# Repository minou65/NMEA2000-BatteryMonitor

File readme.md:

# NMEA Battery monitor

## Table of contents
- [NMEA Battery monitor](#nmea-battery-monitor)
	- [Table of contents](#table-of-contents)
	- [Description](#description)
	- [Disclaimer](#disclaimer)
	- [Schema](#schema)
	- [NMEA 2000](#nmea-2000)
	- [Librarys](#librarys)
	- [Part list](#part-list)
		- [Shunt housing](#shunt-housing)
	- [Running values](#running-values)
		- [Battery voltage](#battery-voltage)
		- [Current](#current)
		- [Avg current](#avg-current)
		- [State of charge (Soc)](#state-of-charge-soc)
		- [Time to go (Ttg)](#time-to-go-ttg)
		- [Battery full](#battery-full)
		- [Temperature](#temperature)
	- [Statistics](#statistics)
	- [Configuration](#configuration)
		- [System configuration](#system-configuration)
			- [Thing name](#thing-name)
			- [AP password](#ap-password)
			- [WiFi SSID](#wifi-ssid)
			- [WiFi password](#wifi-password)
			- [start AP only at boot sequence](#start-ap-only-at-boot-sequence)
			- [AP offline mode after (minutes)](#ap-offline-mode-after-minutes)
		- [NEMA configuration](#nema-configuration)
			- [Instance](#instance)
			- [SID](#sid)
		- [Shunt settings](#shunt-settings)
			- [Shunt resistance \[Ω\] __\*__](#shunt-resistance-ω-)
			- [Expected max current \[A\] __\*__](#expected-max-current-a-)
			- [Voltage calibration factor](#voltage-calibration-factor)
			- [Current calibration factor](#current-calibration-factor)
		- [Battery](#battery)
			- [Type __\*__](#type-)
			- [Voltage __\*__](#voltage-)
			- [Chemistry __\*__](#chemistry-)
			- [Capacity __\*__](#capacity-)
			- [charge efficiency \[%\]](#charge-efficiency-)
			- [Minimum SOC \[%\]](#minimum-soc-)
			- [Replacement date](#replacement-date)
			- [Manufacturer](#manufacturer)
		- [Battery full detection](#battery-full-detection)
			- [Voltage when full \[V\] __\*__](#voltage-when-full-v-)
			- [Tail current \[A\] __\*__](#tail-current-a-)
			- [Delay before full \[s\] __\*__](#delay-before-full-s-)
			- [Current threshold](#current-threshold)
			- [Statistics Page](#statistics-page)
	- [Username and password](#username-and-password)
	- [Default IP address](#default-ip-address)
	- [Firmware Update](#firmware-update)
	- [Blinking codes](#blinking-codes)
	- [Reset](#reset)

## Description
The INA226 is a versatile current and power monitor chip that can be used to create a battery monitor. It measures both voltage and current, taking into account the direction of current flow (whether it’s from or to the battery). Based on the configured ampere-hours (Ah), current, and voltage, it calculates the battery's state of charge.

Here are some key details about the INA226:
- Voltage Measurement Range: 0V to 36V DC
- Shunt Voltage Range (for current measurement): ±82mV
- The INA226 can handle shunt voltages as low as 60mV and as high as 82mV, depending on the current and the shunt resistor used

The INA226 should be connected to the shunt so that charges going into the battery are positive and those coming out of the battery are negative.

 The system communicates via the NMEA 2000 protocol, sending temperature values and alarms as NMEA 2000 messages over an NMEA bus. Configuration is done through a web interface, and real-time values can be viewed on a website. Additionally, there's a link on the configuration page for convenient firmware updates.

 ## Disclaimer
 | | |
 |-|-----------------|
 |  | Always use a fuse in the + line from the battery to the sensor!! |
 |  | Be careful when using metal tools in the vicinity of batteries. Dropping a metal tool onto a battery might cause a short circuit and possibly an explosion. |

## Schema

## NMEA 2000
The following PGN's will be send
- 127506
- 127508
- 127513

## Librarys 

The Software has been created using Visual Studio with the addon Visual Micro. In order to build it you also need some libraries.

- Wire
- [OneWire (2.3.7)](https://github.com/PaulStoffregen/OneWire)
- [DallasTemperature (3.9.0)](https://github.com/milesburton/Arduino-Temperature-Control-Library)
- [NMEA2000](https://github.com/ttlappalainen/NMEA2000)
- [NMEA2000_ESP32](https://github.com/ttlappalainen/NMEA2000_esp32)
- [AsyncTCP (3.2.6) __*__](https://github.com/mathieucarbou/AsyncTCP)
- [ESPAsyncWebServer (3.3.12) __*__](https://github.com/mathieucarbou/ESPAsyncWebServer)
- [WebSerial (2.0.7) __*__](https://github.com/ayushsharma82/WebSerial)
- [IotWebConf](https://github.com/minou65/IotWebConf)
- [IotWebConfAsync (1.0.2) __*__](https://github.com/minou65/IotWebConfAsync)
- [IotWebRoot](https://github.com/minou65/IotWebRoot)
- [ArduinoJson](https://github.com/bblanchon/ArduinoJson)
- [Preferences](https://github.com/espressif/arduino-esp32/tree/master/libraries/Preferences) (ESP32 built-in)
- [WiFi](https://github.com/espressif/arduino-esp32/tree/master/libraries/WiFi) (ESP32 built-in)
- [Update](https://github.com/espressif/arduino-esp32/tree/master/libraries/Update) (ESP32 built-in)

__*__ new version and/or new repo

## Part list
| Part | Value | Supplier |
| --- | --- | --- |
| D1 | 1N4001 | Reichelt |
| ESP1 | ESP32DEVKITV1 | [ebay](https://www.ebay.ch/itm/204191675506?var=504772734176) |
| IC1 | R-78E05-1.0 | Reichelt |
| IC2 | INA226 | [ebay](https://www.ebay.ch/itm/314750066199) |
| IC3 | MCP2562 | Reichelt oder [ebay](https://www.ebay.ch/itm/364610349378) |
| R1 | 4.7k | Reichelt |
| R2 | Shunt | [ebay](https://www.ebay.ch/itm/164378822180?var=463997139291) |
| X1 | AKL 057-03 | Reichelt |
| X2 | AKL 057-02 | Reichelt |
| X3 | PSS 254/3G | Reichelt |

__Before you can use the sensor board you have to remove the shunt resistor soldered to that board and instead use a bigger shunt, e.g. a 100A/75mV.__

You also need a __shunt__, since the small resistor on the board (__dont forget to remove it!__) will not survive the high currents.
There are plenty of options out there. Make sure that you select a resistor appropriate for the currents you expect. I'm using a 100A/75mV shunt.

If you have a 48V System, be aware of the fact that the INA226 does only support voltages up to 36V (40V max). You need a voltage divider to make shure your sensor is not destroyed. 
The code assumes that you use a __470KOhm and a 1MOhm__ resistor, measuring across the 1MOhm towards GND. `( + --470K-- --1M -- GND )` The smaller you choose the small resistor in comparison to the bigger one, the more accurate the measurement will be.

### Shunt housing
In the stl folder you will find a housing for the shunt.

## Running values
### Battery voltage

### Current
Current in amperes flowing through the shunt. If the current is positiv, the battery is being charged. If it is negative, the battery is being discharged.
See [Current calibration factor](#current-calibration-factor) for more information.

### Avg current
The average current consumption in the last 60 seconds.

### State of charge (Soc)
Shows the charge level of the battery. This is calculated based on the capacity and the Ah consumed and is an estimate based on the current consumption.

If no shunt is used and the current calibration factor is set to 0, the following table is used to calculate the Soc

### Time to go (Ttg)
If the time is 00:00, then the battery is charging. Otherwise, it will display an estimate in hours and minutes of how long, based on the current consumption, it will take until the battery is empty.

### Battery full
true or false

### Temperature

## Statistics

## Configuration
After the first boot, there are some values needs to be set up.
These items are maked with __*__ (star) in the list below.

### System configuration

#### Thing name
Please change the name of the device to a name you think describes it the most. It is advised to incorporate a location here in case you are planning to set up multiple devices in the same area. You should only use english letters, and the "_" underscore character. Thus, must not use Space, dots, etc. E.g. `main_cabin` __*__

#### AP password
This password is used, when you want to access the device later on. You must provide a password with at least 8, at most 32 characters. You are free to use any characters, further more you are encouraged to pick a password at least 12 characters long containing at least 3 character classes. __*__

#### WiFi SSID
The name of the WiFi network you want the device to connect to. __*__

#### WiFi password
The password of the network above. Note, that unsecured passwords are not supported in your protection. __*__

#### start AP only at boot sequence
This checkbox, when selected, ensures that the Access Point (AP) is initiated only after the system's boot sequence for the time set in the Startup delay. This can be useful for optimizing system performance and security by preventing the AP from starting at other times, which could potentially lead to unauthorized access or unnecessary resource consumption.

The difference to the setting AP offline mode is that after a successful connection to a WiFi, if the connection is lost, it will not fall back to AP mode.

#### AP offline mode after (minutes)
If you don’t plan to connect the sensor to a WiFi network, you don’t need to configure the two options above. If you want to disable the WiFi after a certain time, you can use this option. Specify how long the WiFi should remain enabled after turning on the sensor. Valid values are from 0 to 30 minutes. A value of 0 means that WiFi is always enabled.

### NEMA configuration
#### Instance
This should be unique at least on one device. May be best to have it unique over all devices sending this PGN. A total of 5 instances are occupied by the device, starting with the number set here. __*__

#### SID
Sequence identifier. In most cases you can use just 255 for SID. The sequence identifier field is used to tie different PGNs data together to same sampling or calculation time.

### Shunt settings
#### Shunt resistance [Ω] __*__
```
R = U / I

U in V
I in A
R in Ohm
```

Assuming a voltage of 75 mV at nominal current, the resulting resistance in ohms will be as follows:

| Shunt Current | Resistance in Ohm | Remarks |
| --- | --- | --- |
| 2 | 100 | Original resistor on the board. |
| 50A | 1.500 |
| 100A | 0.750 |
| 200A | 0.375 |
| 300A | 0.250 |

#### Expected max current [A] __*__
Maximum current that may flow through the shunt

#### Voltage calibration factor
Use a multimeter to measure the voltage on the battery. The measured voltage divided by the voltage displayed by the battery monitor gives the factor that you enter here.

#### Current calibration factor
Use a multimeter to measure the current at the shunt. The measured current, divided by the current displayed by the battery monitor, gives the factor that you need to enter here.

Normally a positive current means that the battery is being charged, a negative current means that it is being discharged. If this is the other way round due to incorrect installation of the shunt, the current can be "reversed" by a negative factor.

If this value is set to 0, no current will be measured. This can be useful if no shunt is installed, such as in a starter battery where only voltage and temperature need to be monitored. See also [State of charge (Soc)](#state-of-charge-soc).

### Battery
#### Type __*__
one of the following
- flooded
- gel
- AGM

#### Voltage __*__
- 6V
- 12V
- 24V
- 32V
- 62V
- 42V
- 48V

Please note that the sensor is built for a maximum voltage of 40V without any special measures!

#### Chemistry __*__
- lead acid
- LiIon
- NiCad
- NiMh

#### Capacity __*__
This parameter is used to tell the battery monitor how big the battery is.

The setting is the battery capacity in Amp-hours (Ah).

#### charge efficiency [%] 
The "Charge Efficiency Factor" compensates for the capacity (Ah) losses during charging. A setting of 100% means that there are no losses.
A charge efficiency of 95% means that 10Ah must be transferred to the battery to get 9.5Ah actually stored in the battery. The charge efficiency of a 
battery depends on battery type, age and usage. The battery monitor takes this phenomenon into account with the charge efficiency factor.

The charge efficiency of a lead acid battery is almost 100% as long as no gas generation takes place. Gassing means that part of the charge current 
is not transformed into chemical energy, which is stored in the plates of the battery, but is used to decompose water into oxygen and hydrogen 
gas (highly explosive!). The energy stored in the plates can be retrieved during the next discharge, whereas the energy used to decompose water is lost. 
Gassing can easily be observed in flooded batteries. Please note that the ‘oxygen only’ end of the charge phase of sealed (VRLA) gel 
and AGM batteries also results in a reduced charge efficiency.

#### Minimum SOC [%]
The minimum SoC is the lowest level of charge that a battery can safely operate at without damaging its cells or reducing its capacity. It is usually expressed as a percentage of the maximum charge. For example, if a battery has a minimum SoC of 10%, it means that it should not be discharged below 10% of its full capacity.

#### Replacement date
The replacement date is the date when the battery was replaced with a new one. It is only for documentation

#### Manufacturer
Manufacturer can be used for documentation

### Battery full detection
#### Voltage when full [V] __*__
The battery voltage must be above this voltage level to consider the battery as fully charged. As soon as the battery monitor detects that the 
voltage of the battery has reached this "charged voltage" parameter and the current has dropped below the "tail current" parameter for a certain 
amount of time, the battery monitor will set the state of charge to 100%.

The following table can help set the correct value

| Type | fully charged |
| --- | --- |
| 12V lead acid | 12.85V |
| 12V AGM | 12.85V |
| 12V LiIon | 12.65V |

#### Tail current [A] __*__
The battery is considered as fully charged once the charge current has dropped to less than this "Tail current" parameter. 
The "Tail current" parameter is expressed as a percentage of the battery capacity.

Note that some battery chargers stop charging when the current drops below a set threshold. In these cases, the tail current must be set 
higher than this threshold.

As soon as the battery monitor detects that the voltage of the battery has reached the set "Charged voltage" parameter and the current has 
dropped below this "Tail current" parameter for a certain amount of time, the battery monitor will set the state of charge to 100%.

#### Delay before full [s] __*__
This is the time the "Voltage when full [V]" parameter and the "Tail current [A]" parameter must be met in order to consider the battery fully charged.

#### Current threshold
When the current measured falls below the "Current threshold" parameter it will be considered zero. The "Current threshold" is used to cancel out very small currents that can negatively affect the long-term state of charge readout in noisy environments. For example, if the actual long-term current is 0.0A and, due to injected noise or small offsets, the battery monitor measures ­0.05A the battery monitor might, in the long term, incorrectly indicate that the battery is empty or will need to be recharged. When the current threshold in this example is set to 0.1A, the battery monitor calculates with 0.0A so that errors are eliminated.

#### Statistics Page

The Statistics page provides detailed information about the performance and status of your device. Here are the key metrics displayed on this page:

- **Min Volt**: Displays the minimum voltage recorded, e.g., 10.5V.
- **Max Volt**: Displays the maximum voltage recorded, e.g., 13.4V.
- **Charged Energy**: Indicates the total energy charged, measured in kWh.
- **Discharged Energy**: Indicates the total energy discharged, measured in kWh.
- **Total Ah Drawn**: Shows the total ampere-hours drawn.
- **Last Discharged Energy**: Displays the energy discharged during the last cycle.
- **Deepest Discharged Energy**: Shows the deepest discharge recorded.
- **Min Temperature**: Displays the minimum temperature recorded.
- **Max Temperature**: Displays the maximum temperature recorded.
- **Charge Cycles**: Indicates the number of charge cycles completed.
- **Auto Syncs**: Shows the number of automatic synchronizations. Auto Syncs occur every time the sensor detects that the battery is full. In this case, the State of Charge (SOC) is set to 100%.
- **Time Since Last Full**: Displays the time elapsed since the battery was last fully charged.

Additionally, there is a **Reset Statistics** button available on this page. Pressing this button will reset all the recorded statistics to their default values. This can be useful for starting fresh measurements or troubleshooting purposes.

These statistics help you monitor the health and performance of your device, ensuring it operates efficiently and effectively.

## Username and password
Username is admin. when not connected to an AP the default password is 123456789.

## Default IP address
When in AP mode, the default IP address is 192.168.4.1

## Firmware Update
To update the firmware, navigate to the Configuration page and click on the Firmware Update link. Follow the on-screen instructions to complete the update process.

## Blinking codes
Previous chapters mentioned blinking patterns, now here is a table summarizing the meaning of the blink codes.

| Blinking Pattern | Meaning |
| --- | --- |
| Rapid blinking <br>(mostly on, interrupted by short off periods) | Entered Access Point mode. This means the device creates its own WiFi network. You can connect to the device with your smartphone or WiFi capable computer. |
| Alternating on/off blinking | Trying to connect to the configured WiFi network. |
| Mostly off with occasional short flash | The device is online. |
| Mostly off with occasional long flash | The device is in offline mode |

## Reset
When CONFIG_PIN is pulled to ground on startup, the Thing will use the initial
password to buld an AP. (E.g. in case of lost password)

Reset pin is GPIO 13

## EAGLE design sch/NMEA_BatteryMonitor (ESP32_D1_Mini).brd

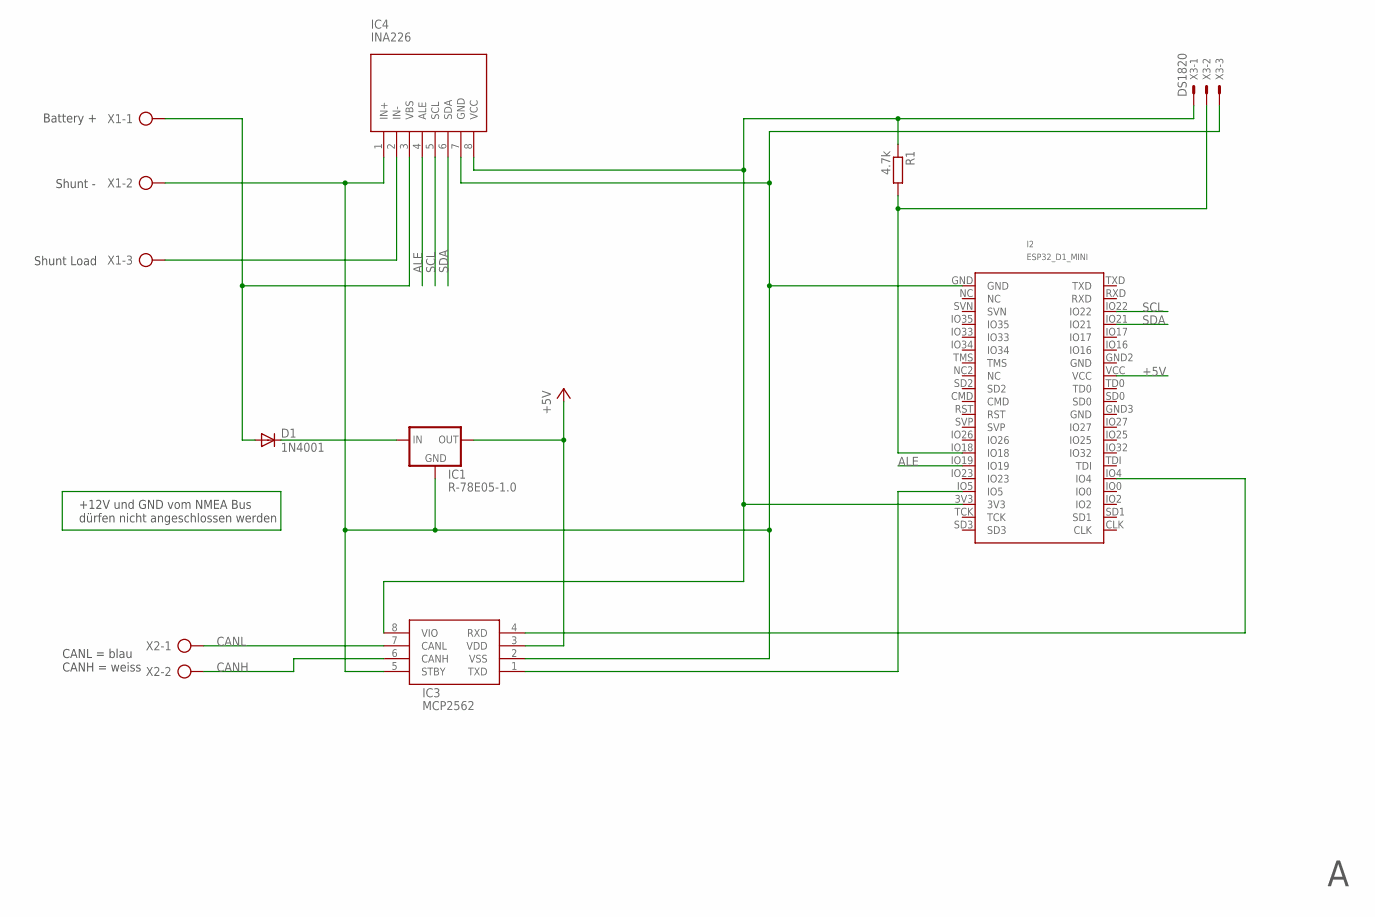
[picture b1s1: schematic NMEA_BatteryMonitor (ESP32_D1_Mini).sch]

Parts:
D1: 1N4001; SOD80
I2: ESP32_D1_MINI
IC1: R-78E05-1.0; R-78E-XX1.0
IC3: MCP2562; SO-8
IC4: INA226
R1: 4.7k; R0805
X1: AK500/3
X2: AK500/2
X3: DS1820; 22-23-2031

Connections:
12V: D1.A, IC4.3 (VBS), X1.1
+5V: I2.VCC, IC1.OUT, IC3.3 (VDD)
ALE: I2.IO19, IC4.4 (ALE)
CANH: IC3.6 (CANH), X2.2
CANL: IC3.7 (CANL), X2.1
GND: I2.GND, IC1.GND, IC3.2 (VSS), IC3.5 (STBY), IC4.1 (IN+), IC4.7 (GND), X1.2, X3.3
LOAD: IC4.2 (IN-), X1.3
unnamed: I2.IO4, IC3.4 (RXD)
unnamed: I2.IO5, IC3.1 (TXD)
unnamed: I2.3V3, IC3.8 (VIO), IC4.8 (VCC), R1.1, X3.1
unnamed: D1.C, IC1.IN
unnamed: I2.IO18, R1.2, X3.2
SCL: I2.IO22, IC4.5 (SCL)
SDA: I2.IO21, IC4.6 (SDA)

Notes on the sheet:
CANL = blau CANH = weiss
Shunt -
Shunt Load
Battery +
+12V und GND vom NMEA Bus dürfen nicht angeschlossen werden

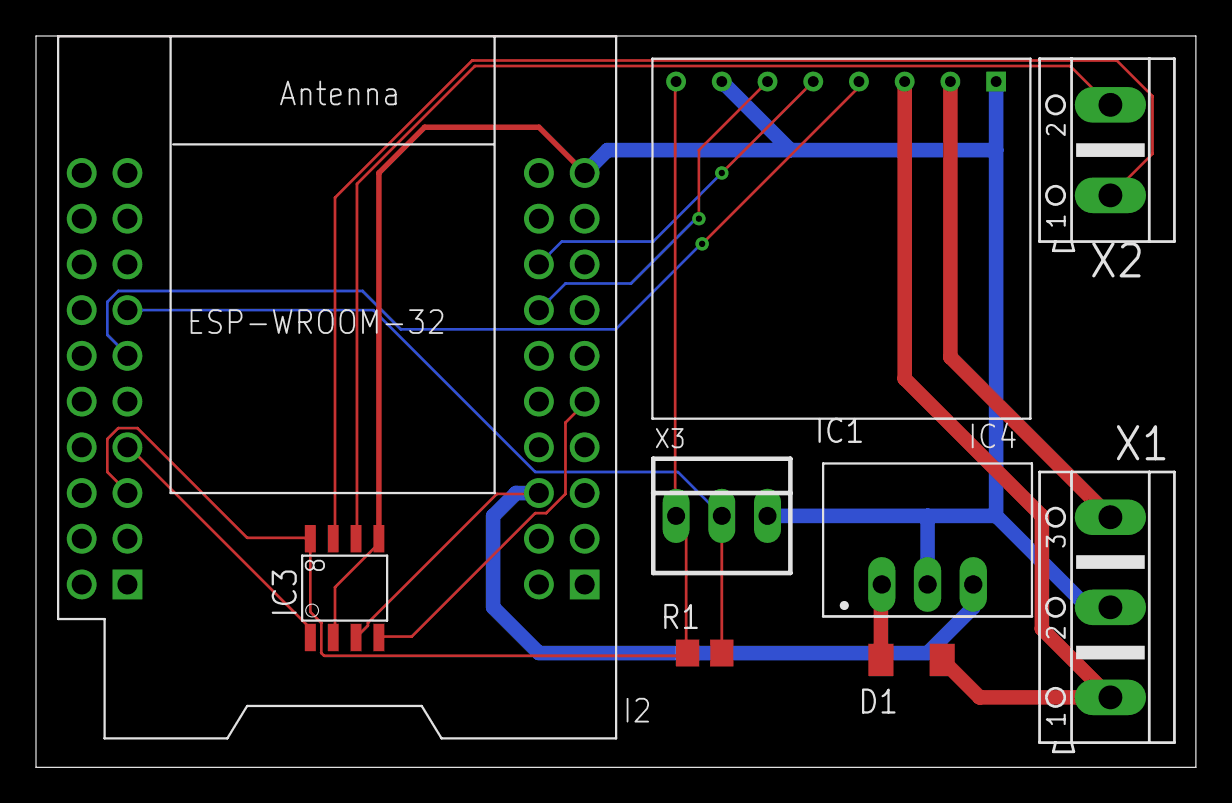
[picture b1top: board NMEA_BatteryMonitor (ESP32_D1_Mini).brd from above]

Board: 2 copper layers, 64.4 x 40.6 mm, 9 parts (0 on the bottom side), 14 nets.

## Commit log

2023-08-05 new file
2023-08-27 get battery type from array
2023-12-26 settings.json excluded
2023-12-26 file renamed
2023-12-26 initial version
2023-12-26 debug info added
2023-12-26 cleanup and debug info added
2023-12-26 BatteryInstance added
2023-12-26 replacment date added
2023-12-26 default value changed
2023-12-28 DATE_LEN added
2023-12-28 config version changed
2023-12-28 Date parameter added and cleanup
2024-01-02 Battery settings added and config version changed
2024-01-02 Battery settings added
2024-01-02 timers changed
2024-01-02 SID added
2024-01-02 store N2k source ID in memory
2024-01-02 store n2k source in eeprom
2024-01-03 vonvert celsius to kelvin
2024-01-03 Version
2024-01-03 fixed some math errors
2024-01-05 fixed read voltage
2024-02-13 doumentation update
2024-02-13 documentation update
2024-02-15 docu updated
2024-02-19 network info added to main page
2024-02-29 version update
2024-03-09 file removed
2024-03-09 class nEMAConfig added
2024-03-21 added firmware upload link to config page
2024-03-22 initial upload
2024-04-24 return to home page link added on config page
2024-04-24 handleData added
2024-04-24 dynamically update the web page
2024-05-01 new layout main page
2024-05-01 when TtG is INFINITY set it on N2K to 8888
2024-05-02 reset pin set
2024-05-02 readme updated
2024-05-03 math for checkfull changed
2024-05-09 hide ap
2024-05-10 removed file
2024-05-10 converted to ESPAsyncWebServer
2024-05-12 main page recreated
2024-05-12 time remaining in seconds
2024-05-12 debug makros added
2024-05-12 include moved to header file
2024-05-12 typo fixed
2024-05-12 external includes
2024-05-13 use arduinJson for generating JSON
2024-05-18 fix a buffer overflow
2024-05-18 fix reading bus when not ready
2024-05-19 for not flodingOnwire bud added a delay for reading tem sensor
2024-05-19 onProgress added for WebSerial outbut
2024-05-19 Revert "onProgress added for WebSerial outbut"
    This reverts commit d8d793680ea8311a2959ac1391c642516a9c2a07.
2024-05-19 Revert "onProgress added for WebSerial outbut"
    This reverts commit bc469ae8f4175641b22e035b5cf81efb3cb0a5a6.
2024-05-19 output progress to WebSerial
2024-05-19 manufacturer added to main page
2024-05-20 float instead of integer
2024-05-21 read current also when it is below gCurrentThreshold
2024-05-21 fixed typos
2024-05-21 output to webserial
2024-05-22 remove file
2024-05-22 clean up
2024-05-25 Don't write status on webserial too often
2024-05-26 use int for TtG (seconds)
2024-05-26 fixed TtG calculation from seconds to HH:mm
2024-05-26 fixed some math errors and added some debug infos
2024-05-26 updateSensor Config
2024-05-30 libs updated
2024-05-30 changed stack size and threat robust
2024-05-30 changed mR to R
2024-05-30 made thread robust
2024-05-31 bug fixing
2024-05-31 auto increment build number
2024-06-01 file updated
2024-06-01 version file added
2024-06-01 build updated
2024-06-01 new build
2024-06-02 output firmware name and version
2024-06-02 some calculation errors and unit errors corrected
2024-06-07 checkFull battery improved
2024-06-08 Use table if no shunt is installed
2024-06-09 allow negativ values for CalibrationFactor
2024-06-09 pass correct values to the bus
2024-06-09 output every 15s battery status
2024-06-10 use preferences for storing statistics
2024-06-10 error in checkfull fixed
2024-06-11 fixed typo
2024-06-11 revertet some changes
2024-06-12 Statistics website added
2024-06-12 statistics website updated
2024-06-12 fix i temp is -127
2024-06-13 linke to main page fixed
2024-06-13 some statistics added
2024-06-15 statistics handling
2024-06-30 gitignore updated
2024-07-03 offline mode added
2024-07-03 partlist added
2024-07-03 added help for removing resistor on ina226
2024-07-03 added some missing values
2024-07-09 schema updated
2024-07-09 prevent float overflow
2024-07-14 total Ah drwan added to statistics
2024-07-14 fixed float overflow
2024-07-21 fixed some bugs in writeStats and readStats
2024-07-21 updated dimenssions
2024-07-22 watchdo added
2024-07-27 disable stat saveing
2024-07-27 no negativ seconds
2024-08-18 Watchdog timer removed
2024-08-18 fixed some errors in statistics handling
2024-10-07 Updated to ESPAsyncWebServer version 3.3.12 and removed dependency on ArduinoJson.
2024-10-09 added time stamp to webserial
2024-10-10 write out true or false
2024-10-11 Fixed bug where redirection to root page doesn’t work after reboot
2024-10-12 use new method AsyncUpdater.isFinished() for rebooting device after firmware updated
2024-10-12 Refactor sensor loop and battery status handling
    - Refactored the sensor loop in SensorHandling.cpp to include a new timer, savePreferenceTimer, which triggers the writing of battery statistics to preferences every 3 hours.
    - Updated the BatteryStatus class in StatusHandling.cpp to include a new member variable, magic, and initialize it with a predefined value.
    - Modified the writeStats() function in StatusHandling.cpp to use Preferences to store the battery statistics in non-volatile memory.
2024-10-28 added thumps.db
2024-12-18 Fix platform detection in webHandling.cpp for ESP32 and ESP8266
2024-12-18 Add ESP MAC header and update version to 1.3.13.258
2025-04-14 Update version to 1.3.13.259 with new build date and time
2025-05-04 Remove unused parameters for pressure and humidity sources in NMEAConfig class
2025-05-04 Update shunt resistance parameter to allow lower minimum value
2025-05-04 Fix preprocessor directive for ESP32 platform detection in webHandling.h
2025-05-04 Increase precision of shunt resistance value in JSON response and HTML display
2025-05-19 Add 'Statistics Page' section to README and clarify current calibration instructions
2025-05-19 Refactor WiFi connection handling: remove unused connectAp function and add failure handler
2025-05-29 Increase precision of shunt resistance value in configuration and display
2025-05-30 Bump version to 1.4.0: update minor and patch numbers, and refresh build date and time
2025-05-30 Increase precision of shunt resistance and voltage display in sensor handling
2025-08-01 Refactor WiFi setup: remove hardcoded hostname and set it dynamically from configuration
2025-08-01 Fix typos and improve clarity in README.md
2025-09-15 new version
2025-09-15 add configuration information in N2kInit
2025-10-26 fix: add battery mode to JSON response, and streamline HTML response construction
2026-01-09 Refactor: migrate to AsyncIotWebConf library
2026-01-09 Refactor library handling and includes
    Added missing library headers (<Wire.h>, <OneWire.h>, <DallasTemperature.h>, <Preferences.h>) to make dependencies explicit and fix compilation issues.
    Unified CAN pin definitions and NMEA2000_CAN initialization in NMEA2000-BatteryMonitor.ino and moved them to the top of the file.
    Removed obsolete or commented‑out code (e.g., watchdog, stack monitoring).
    Reorganized includes in NMEAHandling.cpp/h and centralized tNMEA2000 handling.
    Bumped version to 1.5.1 for improved compatibility and maintainability across development environments.
    Bibliotheksorganisation verbessert, Code aufgeräumt
2026-01-11 Revert "Refactor library handling and includes"
    This reverts commit ac40590587ba705850a5181539441795a9495458.
2026-01-11 Refactor: reverted includes from header file
2026-02-21 feat: add support for apple-touch-icon in web responses
2026-02-21 new favicon
2026-04-25 Refactor: update watchdog timer configuration and cleanup
2026-04-25 feat: add logRebootReason function to track reboot count and reason
2026-04-25 fix: reset watchdog timer in loop2 to prevent system resets
2026-04-26 feat: enhance reboot logging with detailed reason and count tracking
2026-05-31 refactor: streamline writeStats and readStats functions for improved clarity and error handling
2026-05-31 refactor: update handleRoot function to use AsyncResponseStream for improved performance and readability
2026-05-31 refactor: replace custom reboot logging with RebootManager for streamlined reboot tracking
2026-06-24 schema removed
2026-06-25 fix: correct shunt resistance calibration in setupSensor and sensorLoop functions
2026-06-26 fix: update current LSB calculations to use INA226_CURRENT_RANGE for accuracy
2026-06-28 refactor: introduce new configuration classes for battery and shunt settings
2026-06-28 refactor: rename variables in SendN2kBattery function for clarity
2026-06-28 refactor: remove unused battery-related variables from common.h
2026-06-28 refactor: update battery and shunt configuration usage in handleData function
2026-06-30 feat: add BatteryConfig, ShuntConfig, and BatteryFullConfig classes for enhanced battery management
2026-06-30 refactor: enhance board configuration options and improve error handling in common.h
2026-06-30 feat: add NMEAConfig class for NMEA configuration management
2026-06-30 feat: implement NMEA2000 message handling for system time and GNSS data
2026-06-30 refactor: remove hardcoded OneWire bus definition and fix temperature logging reference
2026-06-30 refactor: rename global battery status variable and update calibration factor references
2026-06-30 refactor: streamline sensor handling by removing unused variables and updating configuration references
2026-06-30 refactor: update variable names and remove unused configurations in web handling
2026-06-30 refactor: enhance setup logging and improve brownout detector handling
